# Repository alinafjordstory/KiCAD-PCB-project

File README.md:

ОТЧЕТ

Подготовила: Данилина Алина, гр. БМТ2-31М

Проект: печатная плата для усилителя ЭЭГ

1. Библиотека компонентов (сабмодуль)
Создан отдельный git-репозиторий KiCAD-libs, который подключен к основному проекту как git-сабмодуль (папка libs).
В библиотеке собраны УГО и посадочные места для всех компонентов схемы.
Для компонентов добавлены 3D-модели (STEP и STP).

2. Схема электрическая принципиальная
Схема перенесена в KiCad и оформлена с рамкой и основной надписью по ГОСТ.
Для всех компонентов в свойствах заведено и заполнено поле Manufacturer_Part_Number с реальными артикулами (с сайта Чип и Дип).

3. Печатная плата
Выполнена трассировка платы с учетом технологических норм завода «Резонит»
(ширина дорожек 0.2 мм, отверстия 0.4 мм, зазоры 0.15 мм, толщина шрифта 1 мм).
Соблюдены принципы DFMA: шелкография не перекрывает контактные площадки, учтены зазоры паяльной маски, обеспечен теплоотвод для стабилизатора.

4. Скрипт автоматизации
В корне проекта создан файл build.bat, который через утилиту kicad-cli автоматически выполняет:
- Проверку ERC (электрические правила),
- Проверку DRC (правила проектирования платы),
- Генерацию Gerber-файлов,
- Генерацию перечня элементов (BOM) в формате CSV.
- Экспорт схемы в PDF.
Все результаты сохраняются в папку output_files (прикреплена в репозитории, при запуске скрипта обновляется).

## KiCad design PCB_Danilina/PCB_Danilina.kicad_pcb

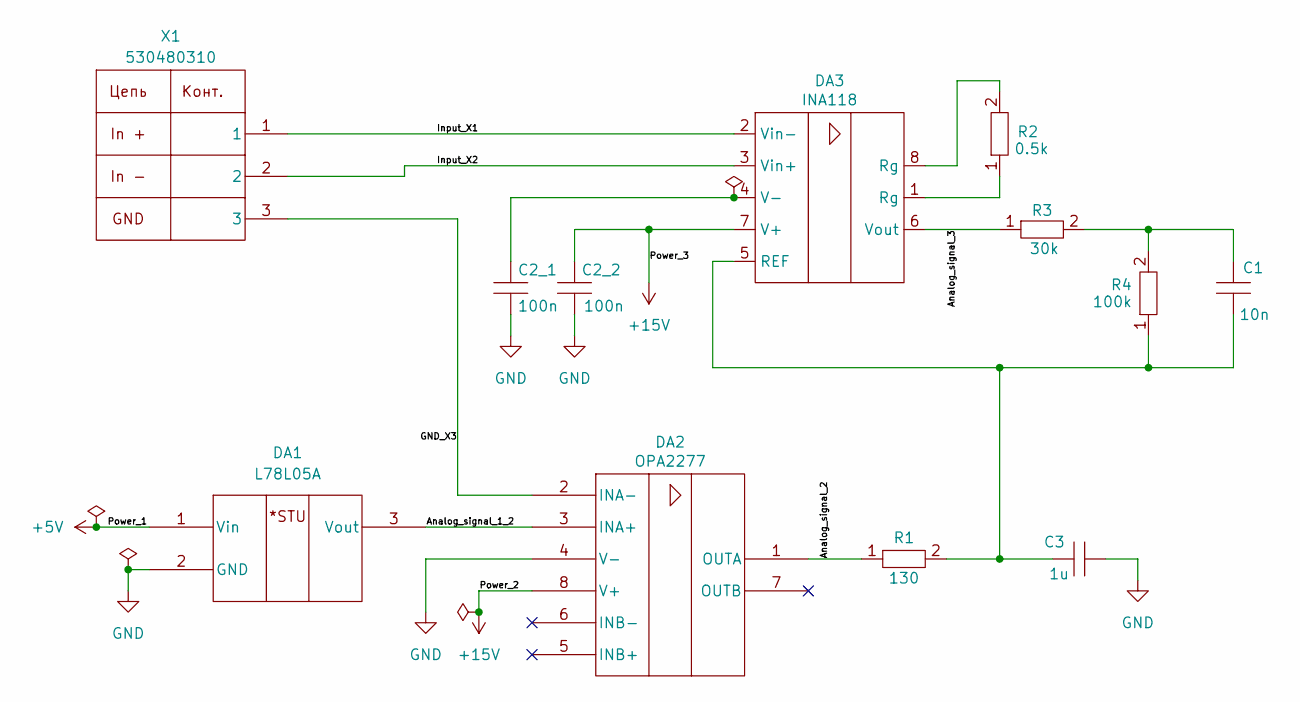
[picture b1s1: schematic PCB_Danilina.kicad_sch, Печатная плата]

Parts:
C1: 10n; CAP_GRM1885; Manufacturer_Part_Number GRM1885C1H103JA01D
C2_1, C2_2: 100n; CAP_GRM155R; Manufacturer_Part_Number GRM31C5C1H104JA01L
C3: 1u; CAP_GRM155R; Manufacturer_Part_Number GRM155R61A105KE15D
DA1: L78L05A; L78L05ACUTR_STM; Manufacturer_Part_Number UMW L78L05A
DA2: OPA2277; OPA2277UA; Manufacturer_Part_Number OPA2277U
DA3: INA118; INA118UB_N; Manufacturer_Part_Number INA118U/2K5
R1: 130; RC0603FR_0730KL; Manufacturer_Part_Number RC0603JR-07130RL
R2: 0.5k; RC0603FR_0730KL; Manufacturer_Part_Number AR03BTCX5000N
R3: 30k; RC0603FR_0730KL; Manufacturer_Part_Number RC0603FR-0730KL
R4: 100k; RC0603FR_0730KL; Manufacturer_Part_Number RC0603FR-07100KL
X1: 530480310; 530480310_MOL; Manufacturer_Part_Number 530480310

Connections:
+5V: DA1.1 (Vin)
+15V: C2_2.1 (5_1), DA2.8 (V+), DA3.7 (V+)
/Analog_signal_1_2: DA1.3 (Vout), DA2.3 (INA+)
/Analog_signal_2: DA2.1 (OUTA), R1.1
/Analog_signal_3: DA3.6 (Vout), R3.1
/GND_X3: DA2.2 (INA-), X1.3
/Input_X1: DA3.2 (Vin-), X1.1
/Input_X2: DA3.3 (Vin+), X1.2
GND: C2_1.2, C2_2.2, C3.2, DA1.2 (GND), DA2.4 (V-)
unnamed: C1.1, R3.2, R4.2
unnamed: C2_1.1 (5_1), DA3.4 (V-)
unnamed: C1.2, C3.1 (5_1), DA3.5 (REF), R1.2, R4.1
unnamed: DA3.1 (Rg), R2.1
unnamed: DA3.8 (Rg), R2.2

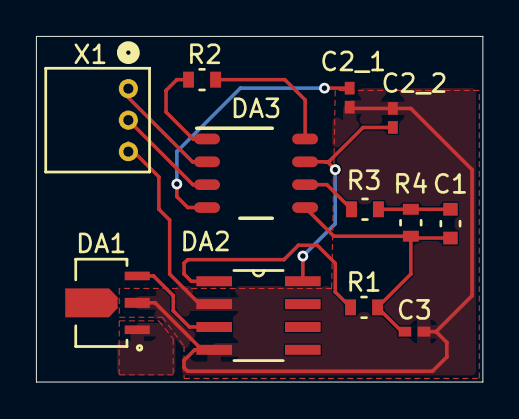
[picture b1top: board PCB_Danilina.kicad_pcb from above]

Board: 2 copper layers, 24.8 x 19.2 mm, 12 parts (0 on the bottom side), 13 nets.
